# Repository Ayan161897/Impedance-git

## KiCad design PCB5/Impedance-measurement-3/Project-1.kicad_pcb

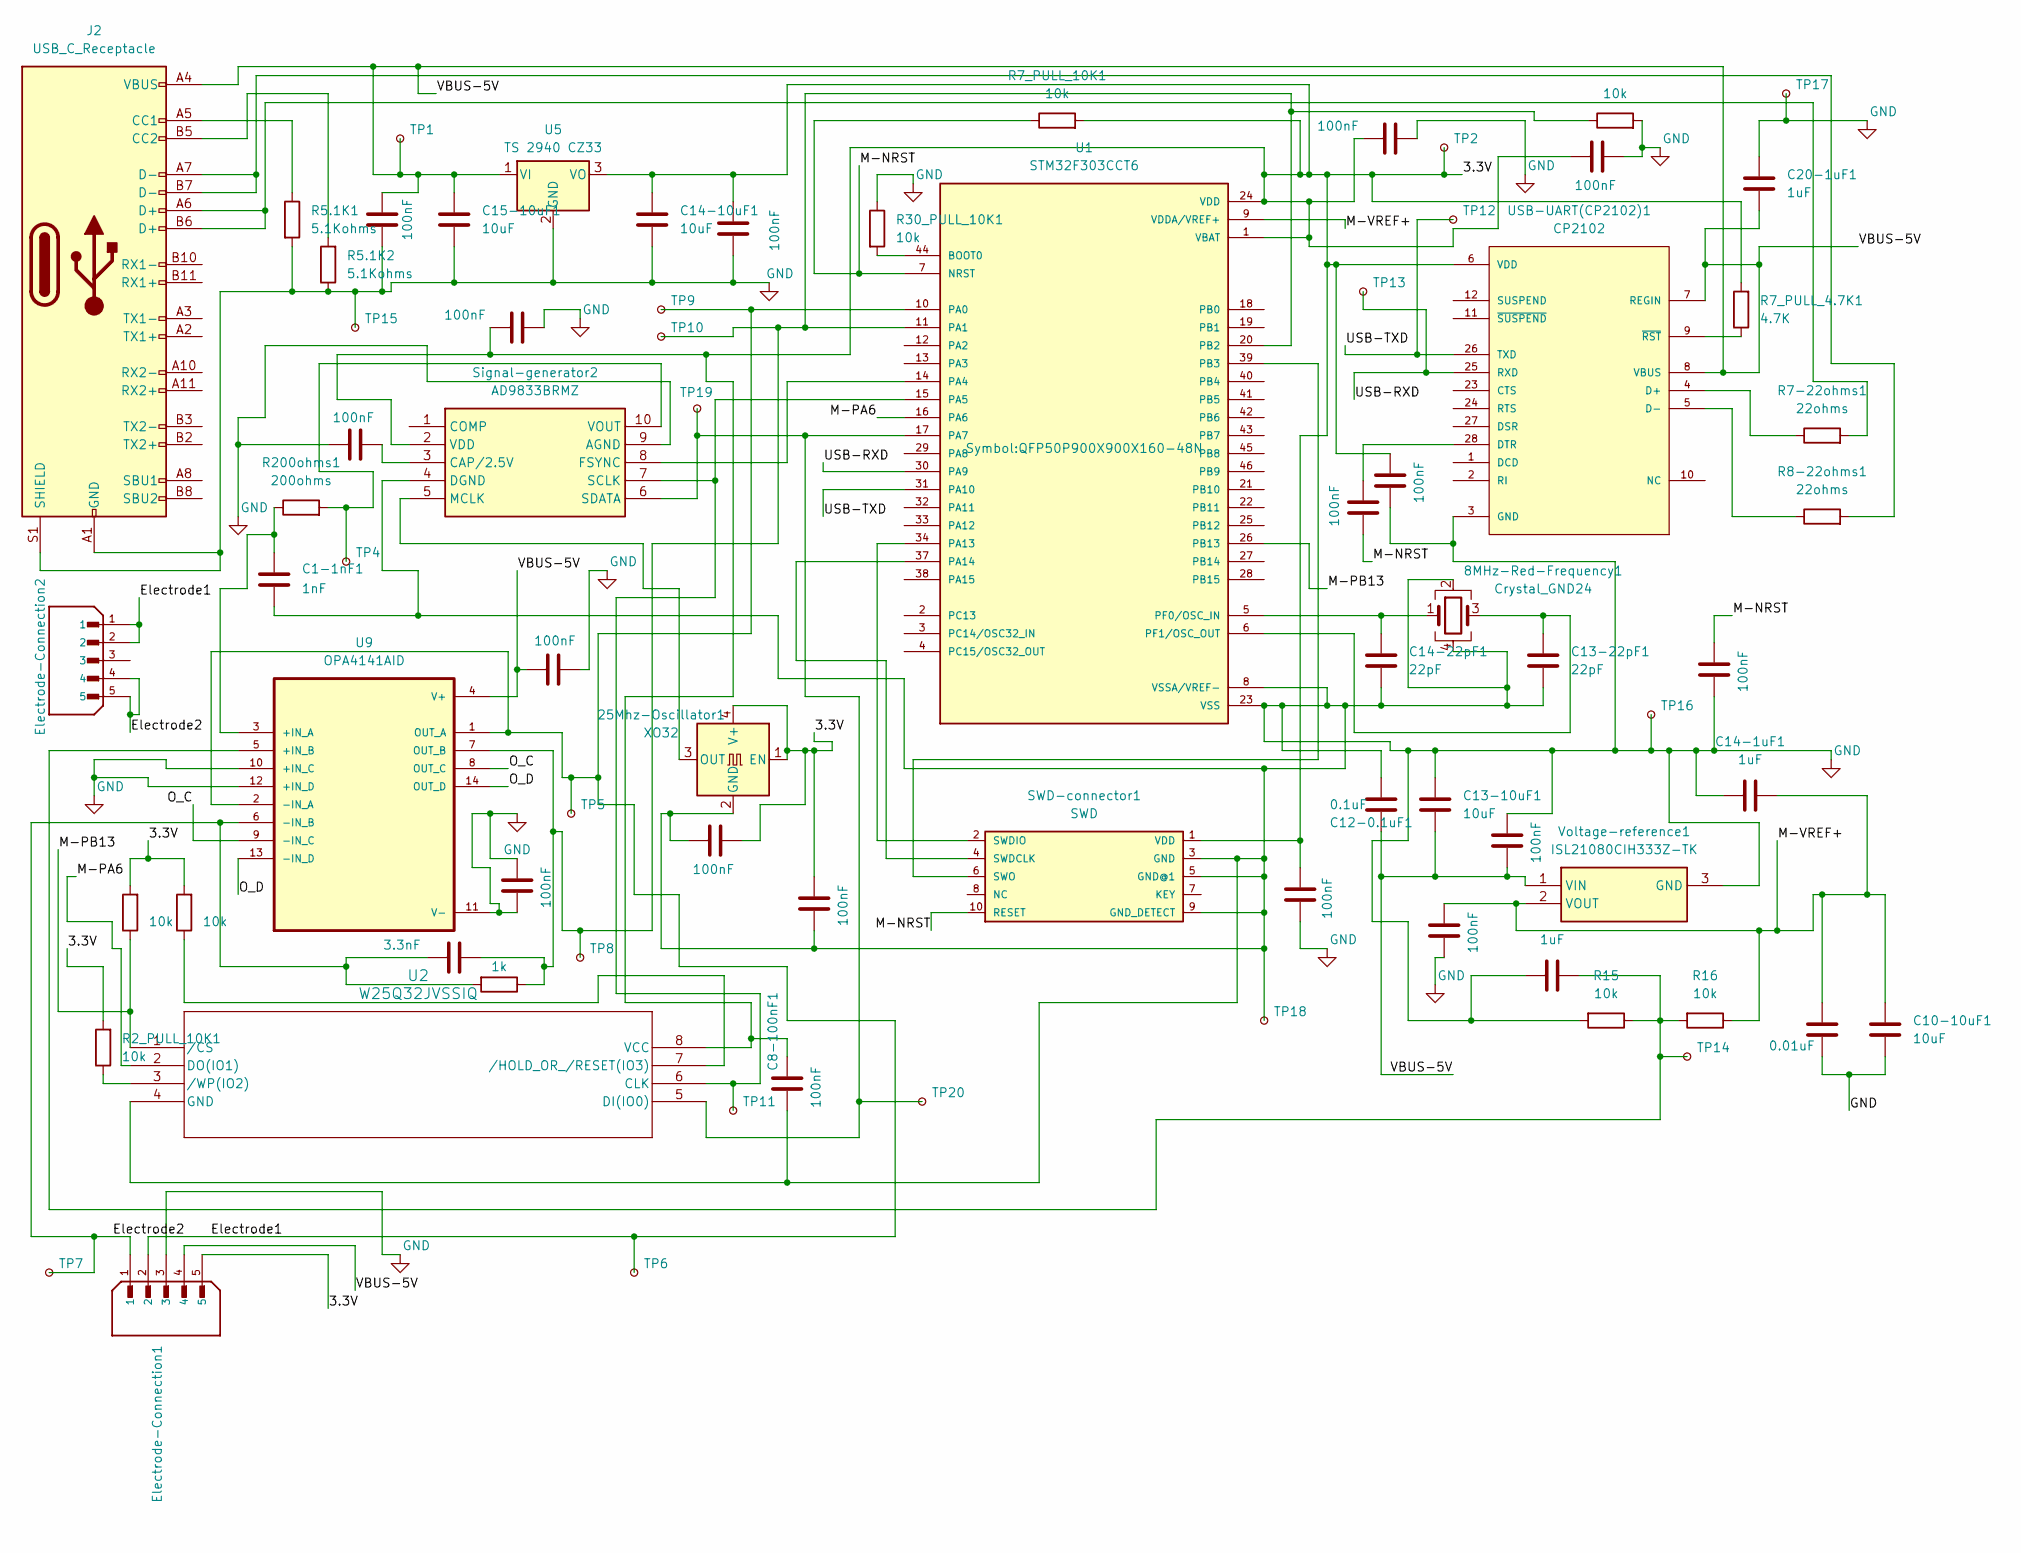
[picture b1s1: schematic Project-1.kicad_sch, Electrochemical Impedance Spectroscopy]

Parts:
8MHz-Red-Frequency1: Crystal_GND24; Crystal_SMD_5032-4Pin_5.0x3.2mm
25Mhz-Oscillator1: XO32; Oscillator_SMD_EuroQuartz_XO32-4Pin_3.2x2.5mm
C1-1nF1: 1nF; C_Axial_L3.8mm_D2.6mm_P7.50mm_Horizontal
C2-100nF1, C3-100nF1, C3-100nF2, C4-100nF1, C5-100nF1, C6-100nF1, C8-100nF1, C9-100nF1, C15-100nF1, C16-100nF1, C17-100nF1, C17-100nF2, C18-100nF1, C19-100nF1, C21-100nF1, C28-100nF1, C31-100nF1: 100nF; C_0805_2012Metric
C10-10uF1, C13-10uF1, C14-10uF1, C15-10uF1: 10uF; C_Axial_L3.8mm_D2.6mm_P7.50mm_Horizontal
C11-0.01uF1: 0.01uF; C_Axial_L3.8mm_D2.6mm_P7.50mm_Horizontal
C11-3.3nF1: 3.3nF; C_Axial_L3.8mm_D2.6mm_P7.50mm_Horizontal
C12-0.1uF1: 0.1uF; C_Axial_L3.8mm_D2.6mm_P7.50mm_Horizontal
C13-22pF1, C14-22pF1: 22pF; C_Axial_L3.8mm_D2.6mm_P7.50mm_Horizontal
C14-1uF1, C17, C20-1uF1: 1uF; C_Axial_L3.8mm_D2.6mm_P7.50mm_Horizontal
Electrode-Connection1, Electrode-Connection2: Cable-connector B5B-XH-A_LF__SN_; JST_B5B-XH-A_LF__SN_; PARTREV 7/4/21
J2: USB_C_Receptacle; USB_C_Receptacle_GCT_USB4115-03-C
R2_PULL_10K1, R3_PULL_10K1, R4_PULL_10K1, R7_PULL_10K1, R15, R16, R25_PULL_10K1, R30_PULL_10K1: 10k; R_Axial_DIN0204_L3.6mm_D1.6mm_P5.08mm_Horizontal
R5.1K1, R5.1K2: 5.1Kohms; R_Axial_DIN0204_L3.6mm_D1.6mm_P5.08mm_Horizontal
R5_1Kohms1: 1k; R_Axial_DIN0204_L3.6mm_D1.6mm_P5.08mm_Horizontal
R7-22ohms1, R8-22ohms1: 22ohms; R_Axial_DIN0204_L3.6mm_D1.6mm_P5.08mm_Horizontal
R7_PULL_4.7K1: 4.7K; R_Axial_DIN0204_L3.6mm_D1.6mm_P5.08mm_Horizontal
R200ohms1: 200ohms; R_Axial_DIN0204_L3.6mm_D1.6mm_P5.08mm_Horizontal
SWD-connector1: SWD; 2X10_BOXHEADER
Signal-generator2: AD9833BRMZ; SOP50P490X110-10N; Mouser Part Number 584-AD9833BRMZ
TP1, TP2, TP4, TP5, TP7, TP8, TP11, TP14, TP15, TP16, TP17, TP18: TestPoint_Small; TestPoint_Pad_D1.5mm
TP6, TP9, TP10, TP12, TP13, TP19, TP20: TestPoint_Small; TestPoint_Pad_D1.0mm
U1: STM32F303CCT6; QFP50P900X900X160-48N; PARTREV 14
U2: W25Q32JVSSIQ; SOIC-8_5.23x5.23mm_P1.27mm
U5: TS 2940 CZ33; TO-220-3_Vertical
U9: OPA4141AID; SOIC127P600X175-14N
USB-UART(CP2102)1: CP2102; QFN50P500X500X100-29N
Voltage-reference1: ISL21080CIH333Z-TK; SOT95P237X112-3N; Mouser Part Number 968-ISL21080CIH333ZT

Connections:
/Electrode1: Electrode-Connection1.2, Electrode-Connection2.1, Electrode-Connection2.2, TP5.1, TP6.1, TP9.1, U1.10 (PA0), U9.1 (OUT_A), U9.2 (-IN_A)
/Electrode2: C11-3.3nF1.1, Electrode-Connection1.1, Electrode-Connection2.4, Electrode-Connection2.5, R5_1Kohms1.2, TP7.1, U9.6 (-IN_B)
/M-NRST: C3-100nF1.1, C5-100nF1.2, R7_PULL_10K1.1, SWD-connector1.10 (RESET), U1.7 (NRST)
/M-PA6: U1.16 (PA6), U2.2 (DO(IO1))
/M-PB13: R3_PULL_10K1.1, U1.26 (PB13), U2.1 (/CS)
/M-VREF+: C10-10uF1.1, C11-0.01uF1.1, C14-1uF1.2, C18-100nF1.2, R16.1, U1.9 (VDDA/VREF+), Voltage-reference1.2 (VOUT)
/O_C: U9.8 (OUT_C), U9.9 (-IN_C)
/O_D: U9.13 (-IN_D), U9.14 (OUT_D)
/USB-RXD: TP13.1, U1.30 (PA9), USB-UART(CP2102)1.25 (RXD)
/USB-TXD: TP12.1, U1.31 (PA10), USB-UART(CP2102)1.26 (TXD)
/VBUS-5V: C2-100nF1.2, C12-0.1uF1.2, C13-10uF1.2, C15-10uF1.1, C20-1uF1.1, C21-100nF1.2, C28-100nF1.1, Electrode-Connection1.4, J2.A4 (VBUS), J2.A9 (VBUS), J2.B4 (VBUS), J2.B9 (VBUS), TP1.1, U5.1 (VI), U9.4 (V+), USB-UART(CP2102)1.7 (REGIN), USB-UART(CP2102)1.8 (VBUS), Voltage-reference1.1 (VIN)
GND: 8MHz-Red-Frequency1.2, 8MHz-Red-Frequency1.4, 25Mhz-Oscillator1.2 (GND), C1-1nF1.2, C2-100nF1.1, C3-100nF2.1, C3-100nF2.2, C4-100nF1.1, C5-100nF1.1, C6-100nF1.1, C8-100nF1.1, C9-100nF1.1, C10-10uF1.2, C11-0.01uF1.2, C12-0.1uF1.1, C13-10uF1.1, C13-22pF1.2, C14-1uF1.1, C14-10uF1.2, C14-22pF1.2, C15-10uF1.2, C15-100nF1.1, C16-100nF1.2, C17.1, C17-100nF1.2, C17-100nF2.1, C18-100nF1.1, C19-100nF1.2, C20-1uF1.2, C21-100nF1.1, C28-100nF1.2, C31-100nF1.1, Electrode-Connection1.3, J2.A1 (GND), J2.A12 (GND), J2.B1 (GND), J2.B12 (GND), J2.S1 (SHIELD), R5.1K1.2, R5.1K2.1, R15.2, R25_PULL_10K1.2, R30_PULL_10K1.1, SWD-connector1.3 (GND), SWD-connector1.5 (GND@1), SWD-connector1.9 (GND_DETECT), Signal-generator2.4 (DGND), Signal-generator2.9 (AGND), TP15.1, TP16.1, TP17.1, TP18.1, U1.8 (VSSA/VREF-), U1.23 (VSS), U1.35 (VSS), U1.47 (VSS), U2.4 (GND), U5.2 (GND), U9.10 (+IN_C), U9.11 (V-), U9.12 (+IN_D), USB-UART(CP2102)1.3 (GND), USB-UART(CP2102)1.29 (GND), Voltage-reference1.3 (GND)
unnamed: 25Mhz-Oscillator1.3 (OUT), Signal-generator2.5 (MCLK)
unnamed: J2.A5 (CC1), R5.1K1.1
unnamed: J2.B5 (CC2), R5.1K2.2
unnamed: J2.A6 (D+), J2.B6 (D+), R7-22ohms1.2
unnamed: J2.A7 (D-), J2.B7 (D-), R8-22ohms1.2
unnamed: SWD-connector1.4 (SWDCLK), U1.37 (PA14)
unnamed: SWD-connector1.2 (SWDIO), U1.34 (PA13)
unnamed: SWD-connector1.6 (SWO), U1.39 (PB3)
unnamed: C15-100nF1.2, Signal-generator2.3 (CAP/2.5V)
unnamed: Signal-generator2.8 (FSYNC), U1.14 (PA4)
unnamed: Signal-generator2.7 (SCLK), TP11.1, U1.15 (PA5), U2.6 (CLK)
unnamed: Signal-generator2.6 (SDATA), TP19.1, TP20.1, U1.17 (PA7), U2.5 (DI(IO0))
unnamed: R200ohms1.2, Signal-generator2.10 (VOUT), TP4.1
unnamed: R30_PULL_10K1.2, U1.44 (BOOT0)
unnamed: C11-3.3nF1.2, R5_1Kohms1.1, R25_PULL_10K1.1, TP8.1, TP10.1, U1.11 (PA1), U1.20 (PB2), U9.7 (OUT_B)
unnamed: 8MHz-Red-Frequency1.1, C14-22pF1.1, U1.5 (PF0/OSC_IN)
unnamed: 8MHz-Red-Frequency1.3, C13-22pF1.1, U1.6 (PF1/OSC_OUT)
unnamed: R4_PULL_10K1.1, U2.7 (/HOLD_OR_/RESET(IO3))
unnamed: R2_PULL_10K1.1, U2.3 (/WP(IO2))
unnamed: C1-1nF1.1, R200ohms1.1, U9.3 (+IN_A)
unnamed: C17.2, R15.1, R16.2, TP14.1, U9.5 (+IN_B)
unnamed: R7-22ohms1.1, USB-UART(CP2102)1.4 (D+)
unnamed: R8-22ohms1.1, USB-UART(CP2102)1.5 (D-)
unnamed: C3-100nF1.2, USB-UART(CP2102)1.28 (DTR)
unnamed: USB-UART(CP2102)1.10 (NC), USB-UART(CP2102)1.13 (NC), USB-UART(CP2102)1.14 (NC), USB-UART(CP2102)1.15 (NC), USB-UART(CP2102)1.16 (NC), USB-UART(CP2102)1.17 (NC), USB-UART(CP2102)1.18 (NC), USB-UART(CP2102)1.19 (NC), USB-UART(CP2102)1.20 (NC), USB-UART(CP2102)1.21 (NC), USB-UART(CP2102)1.22 (NC)
unnamed: R7_PULL_4.7K1.1, USB-UART(CP2102)1.9 (~RST)
VDD: 25Mhz-Oscillator1.1 (EN), 25Mhz-Oscillator1.4 (V+), C4-100nF1.2, C6-100nF1.2, C8-100nF1.2, C9-100nF1.2, C14-10uF1.1, C16-100nF1.1, C17-100nF1.1, C17-100nF2.2, C19-100nF1.1, C31-100nF1.2, Electrode-Connection1.5, R2_PULL_10K1.2, R3_PULL_10K1.2, R4_PULL_10K1.2, R7_PULL_4.7K1.2, R7_PULL_10K1.2, SWD-connector1.1 (VDD), Signal-generator2.2 (VDD), TP2.1, U1.1 (VBAT), U1.24 (VDD), U1.36 (VDD), U1.48 (VDD), U2.8 (VCC), U5.3 (VO), USB-UART(CP2102)1.6 (VDD)

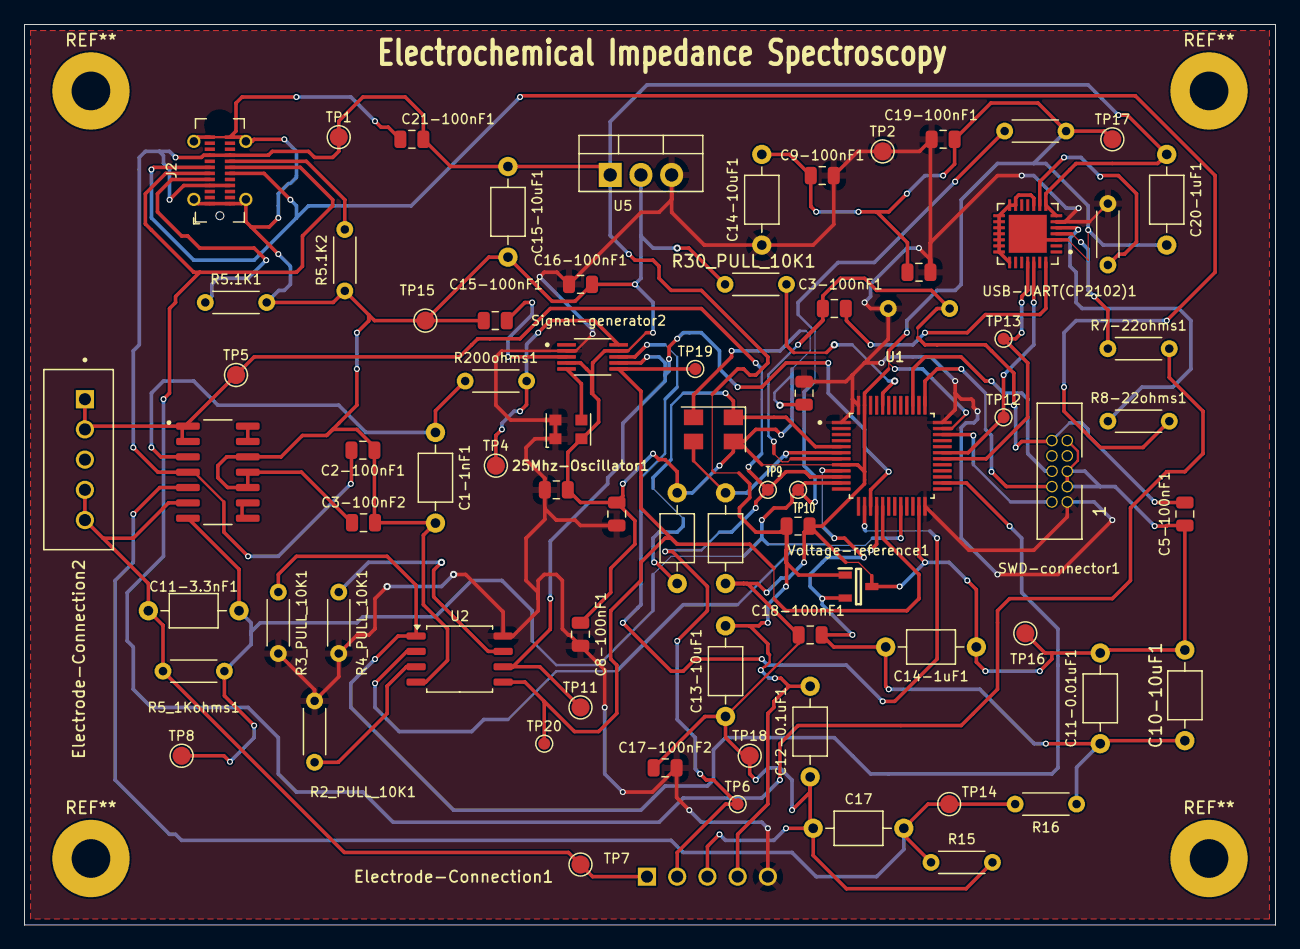
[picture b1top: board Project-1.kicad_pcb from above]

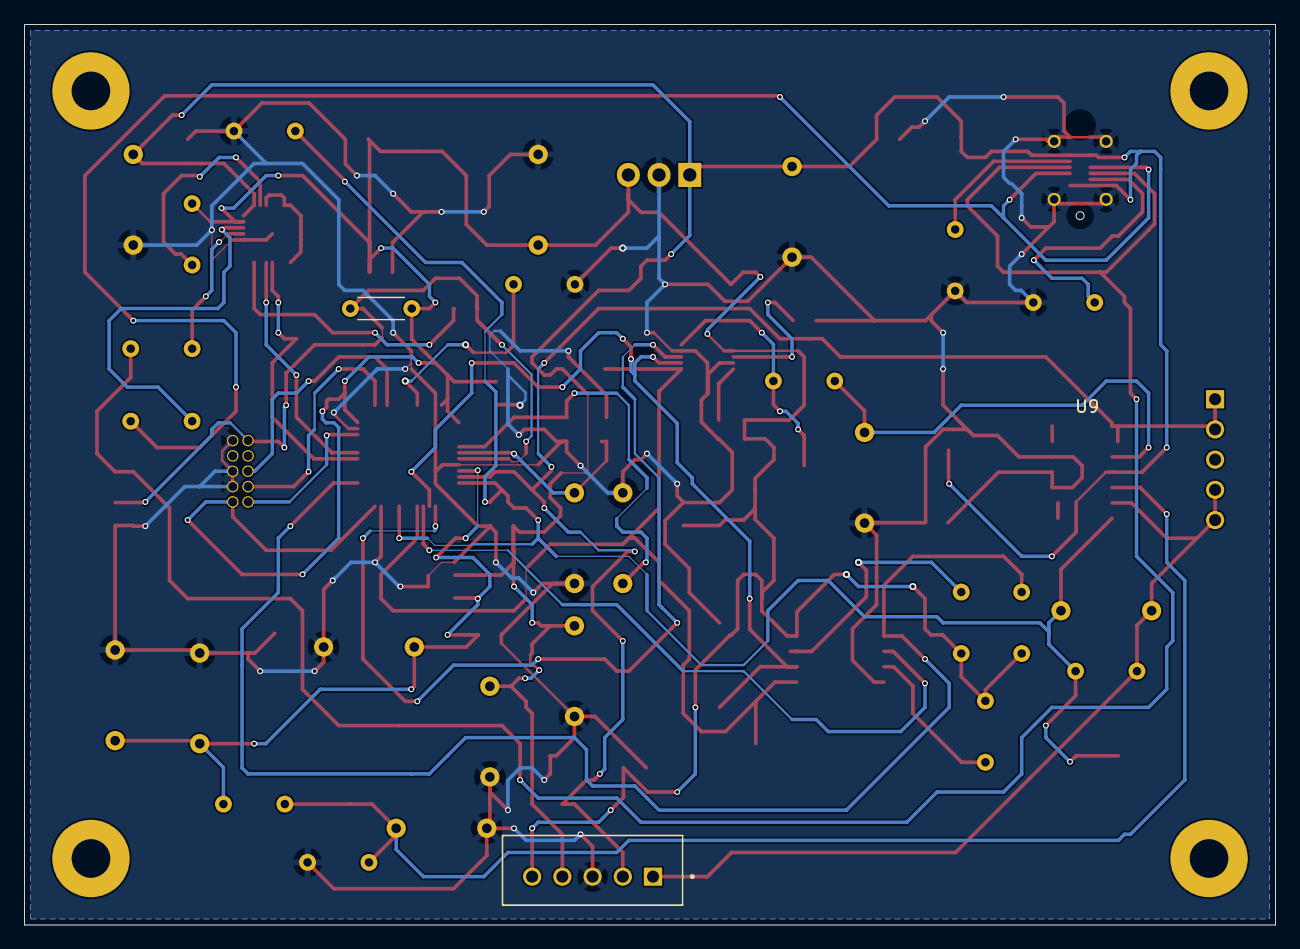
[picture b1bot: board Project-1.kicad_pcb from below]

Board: 2 copper layers, 103.5 x 74.5 mm, 77 parts (2 on the bottom side), 39 nets.

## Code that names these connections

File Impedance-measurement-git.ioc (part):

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Mcu.Name=STM32F303C(B-C)Tx
Mcu.Package=LQFP48
Mcu.UserName=STM32F303CCTx
PA0.Mode=IN1-Single-Ended
PA0.Signal=ADC1_IN1
PA1.Mode=IN2-Single-Ended
PA1.Signal=ADC1_IN2
PA10.Mode=Asynchronous
PA10.Signal=USART1_RX
PA13.Mode=Trace_Asynchronous_SW
PA13.Signal=SYS_JTMS-SWDIO
PA14.Mode=Trace_Asynchronous_SW
PA14.Signal=SYS_JTCK-SWCLK
PA4.GPIOParameters=GPIO_Speed,PinState,GPIO_Label
PA4.GPIO_Label=AD9833_FSYNC
PA4.GPIO_Speed=GPIO_SPEED_FREQ_HIGH
PA4.PinState=GPIO_PIN_SET
PA4.Signal=GPIO_Output
PA5.Mode=Full_Duplex_Master
PA5.Signal=SPI1_SCK
PA6.Mode=Full_Duplex_Master
PA6.Signal=SPI1_MISO
PA7.Mode=Full_Duplex_Master
PA7.Signal=SPI1_MOSI
PA9.Mode=Asynchronous
PA9.Signal=USART1_TX
PB12.GPIOParameters=GPIO_Speed,PinState,GPIO_Label
PB12.GPIO_Label=W25Q32_CS
PB12.GPIO_Speed=GPIO_SPEED_FREQ_HIGH
PB12.PinState=GPIO_PIN_SET
PB12.Signal=GPIO_Output
PB13.GPIOParameters=GPIO_Label
PB13.GPIO_Label=STATUS_LED
PB13.Signal=GPIO_Output
PB2.Signal=GPIO_Analog
PB3.Mode=Trace_Asynchronous_SW
PB3.Signal=SYS_JTDO-TRACESWO
PF0-OSC_IN.Mode=HSE-External-Oscillator
PF0-OSC_IN.Signal=RCC_OSC_IN
PF1-OSC_OUT.Mode=HSE-External-Oscillator
PF1-OSC_OUT.Signal=RCC_OSC_OUT
RCC.HSEPLLFreq_Value=8000000
RCC.HSE_VALUE=8000000
RCC.SYSCLKFreq_VALUE=72000000
RCC.SYSCLKSourceVirtual=RCC_SYSCLKSOURCE_PLLCLK
board=custom

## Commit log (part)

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2026-05-22 Fix build errors: add missing ADC and SPI HAL drivers, enable modules in hal_conf
    The project used ADC and SPI peripherals but the required HAL driver files were
    missing from the repository and both modules were disabled in hal_conf.h.
    - Add stm32f3xx_hal_adc.h/c, stm32f3xx_hal_adc_ex.h/c, stm32f3xx_hal_spi.h/c
    and stm32f3xx_hal_spi_ex.h from the official STM32F3xx HAL driver library
    - Enable HAL_ADC_MODULE_ENABLED and HAL_SPI_MODULE_ENABLED in stm32f3xx_hal_conf.h
    - Update Debug/Drivers/.../subdir.mk to compile the new ADC and SPI source files
2026-05-28 Update local changes
2026-05-28 Update SPI included
2026-05-30 Update 30/05/2026 cubemx configured
